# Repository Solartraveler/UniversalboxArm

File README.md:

# UniversalboxArm

## Idea

Have a box for experiments and easy testing with a CPU which is more powerful than an AVR (Arduino)
and uses less energy than a Raspberry Pi.
Then add some common peripherals and fit this into a case.

## Features

The following hardware has been added. Not everything is required to be populated on the PCB.

- Various 64Pin STM32 MCUs possible

    - STM32L452RET (80MHz, 160KiB RAM) tested

- Runs from USB power

- Can run from a LiFePO battery and charge it

- 2x red-green duo LEDs

- Four buttons

- LCD socket

    - 128x128 (ST7735, tested), 160x128 (ST7735, untested) or 320x240 (ILI9341, tested) RGB LCDs are possible

- Four Relays

- External flash with up to 8MiB

- RS232 level converter

- IR receiver

- WLAN with an ESP-01

- Two open collector outputs

- Several ESD protected in and outputs

- AVR coprocessor for resetting and charge control

## Status

### Software

#### DFU loader for the ARM

A loader for the STM32 MCU is feature complete.

- Can be used by the common dfu-util delivered by the usual Linux distributions (like Debian)

- Accepts applications within a common .tar file together with some metadata

    - With the STM32L452 having 160KiB RAM, the tar file may be up to 128KiB in size.
Needing 2.5KiB overhead for the .tar format and the metadata, the binary may be up to 125.5KiB in size and after starting can use the full 160KiB for code + data.
Executing from RAM results in about 80% of the speed compared with executing from flash with the same CPU frequency.

- The application can be run directly from the RAM or stored into the external flash

    - Transferring to RAM is much faster than writing to the flash. Also there is no worry about the internal flash lifetime.

- Formats the external flash as FAT filesystem

- Allows configuring one of the three LCD sizes

    - Configuration is stored on the external flash and can be read by other applications

- With the four keys and the LCD, applications can be selected from the external flash and run without an USB connection

    - Can set one application as autostarting on power-on

- Each application can have a short descriptive text and explanation image to be shown on the LCD

    - The text can be up to 1KiB long and is taken from the readme.md of each firmware

    - The image is 3 bit RGB and must have the size of the selected LCD or one of the possible smaller LCDs.
Moreover the compressed data needs to fit within 7000byte. Due to RAM constraints, each 4x4 pixel block can not display pixel with more than two different colors.

#### Firmware for the coprocessor

- A long press of the left key resets the ARM processor

- A long press of the right key toggles if a reset should start the DFU bootloader from ST or the application from the flash (most likely the DFU bootloader described above)

- Supports a SPI communication to the ARM processor

    - ARM processor can request a reset

    - ARM processor can enable a watchdog

- The battery can be charged

- A wakeup time for the ARM processor can be set

#### More software

Software testing all the hardware to be working as intended has been written for the ARM processor and the AVR coprocessor.

There is a implementation for using the 8MiB flash as USB pen drive.

One application implements an NTP client and uses the display as digital clock.

See [readme.md](src/apps/readme.md)

### Hardware

The PCB version 1 is working, but a lot of patching is required at several peripherals to use them.
With 380µA, the power down consumption is too high, as this would discharge a full battery within 65 days, and then the LiFePo must be considered defective.
The required changes are documented. Recreating a PCB version 1 is discouraged.
Instead the required changes need to be integrated into a version 2.

Milling the case is done.

See [readme.md](case/readme.md)

## Using a breadboard

Without soldering an own PCB, some of the apps can be used together with a Nucleo evaluation board from ST.
Then it is just a connection of some wires.
Instead of the onboard flash, the SD card can be used to store settings.
Many of the breakout boards for the LCDs already have a SD card slot on the backside.
The serial port is provided by the nucleo board over USB itself.
One LED and one button is provided by the nucleo board, thee additional buttons can be connected, everthing else is currently missing support.
Currently only the blinky-hal, test-everything and adc-scope apps have been tested on a nucleo with a STM32F411.
As the used board with a STM32F411 only has 128KiB of RAM, it will never be possible to load and execute all apps from RAM there.
However all could made working when running from flash.

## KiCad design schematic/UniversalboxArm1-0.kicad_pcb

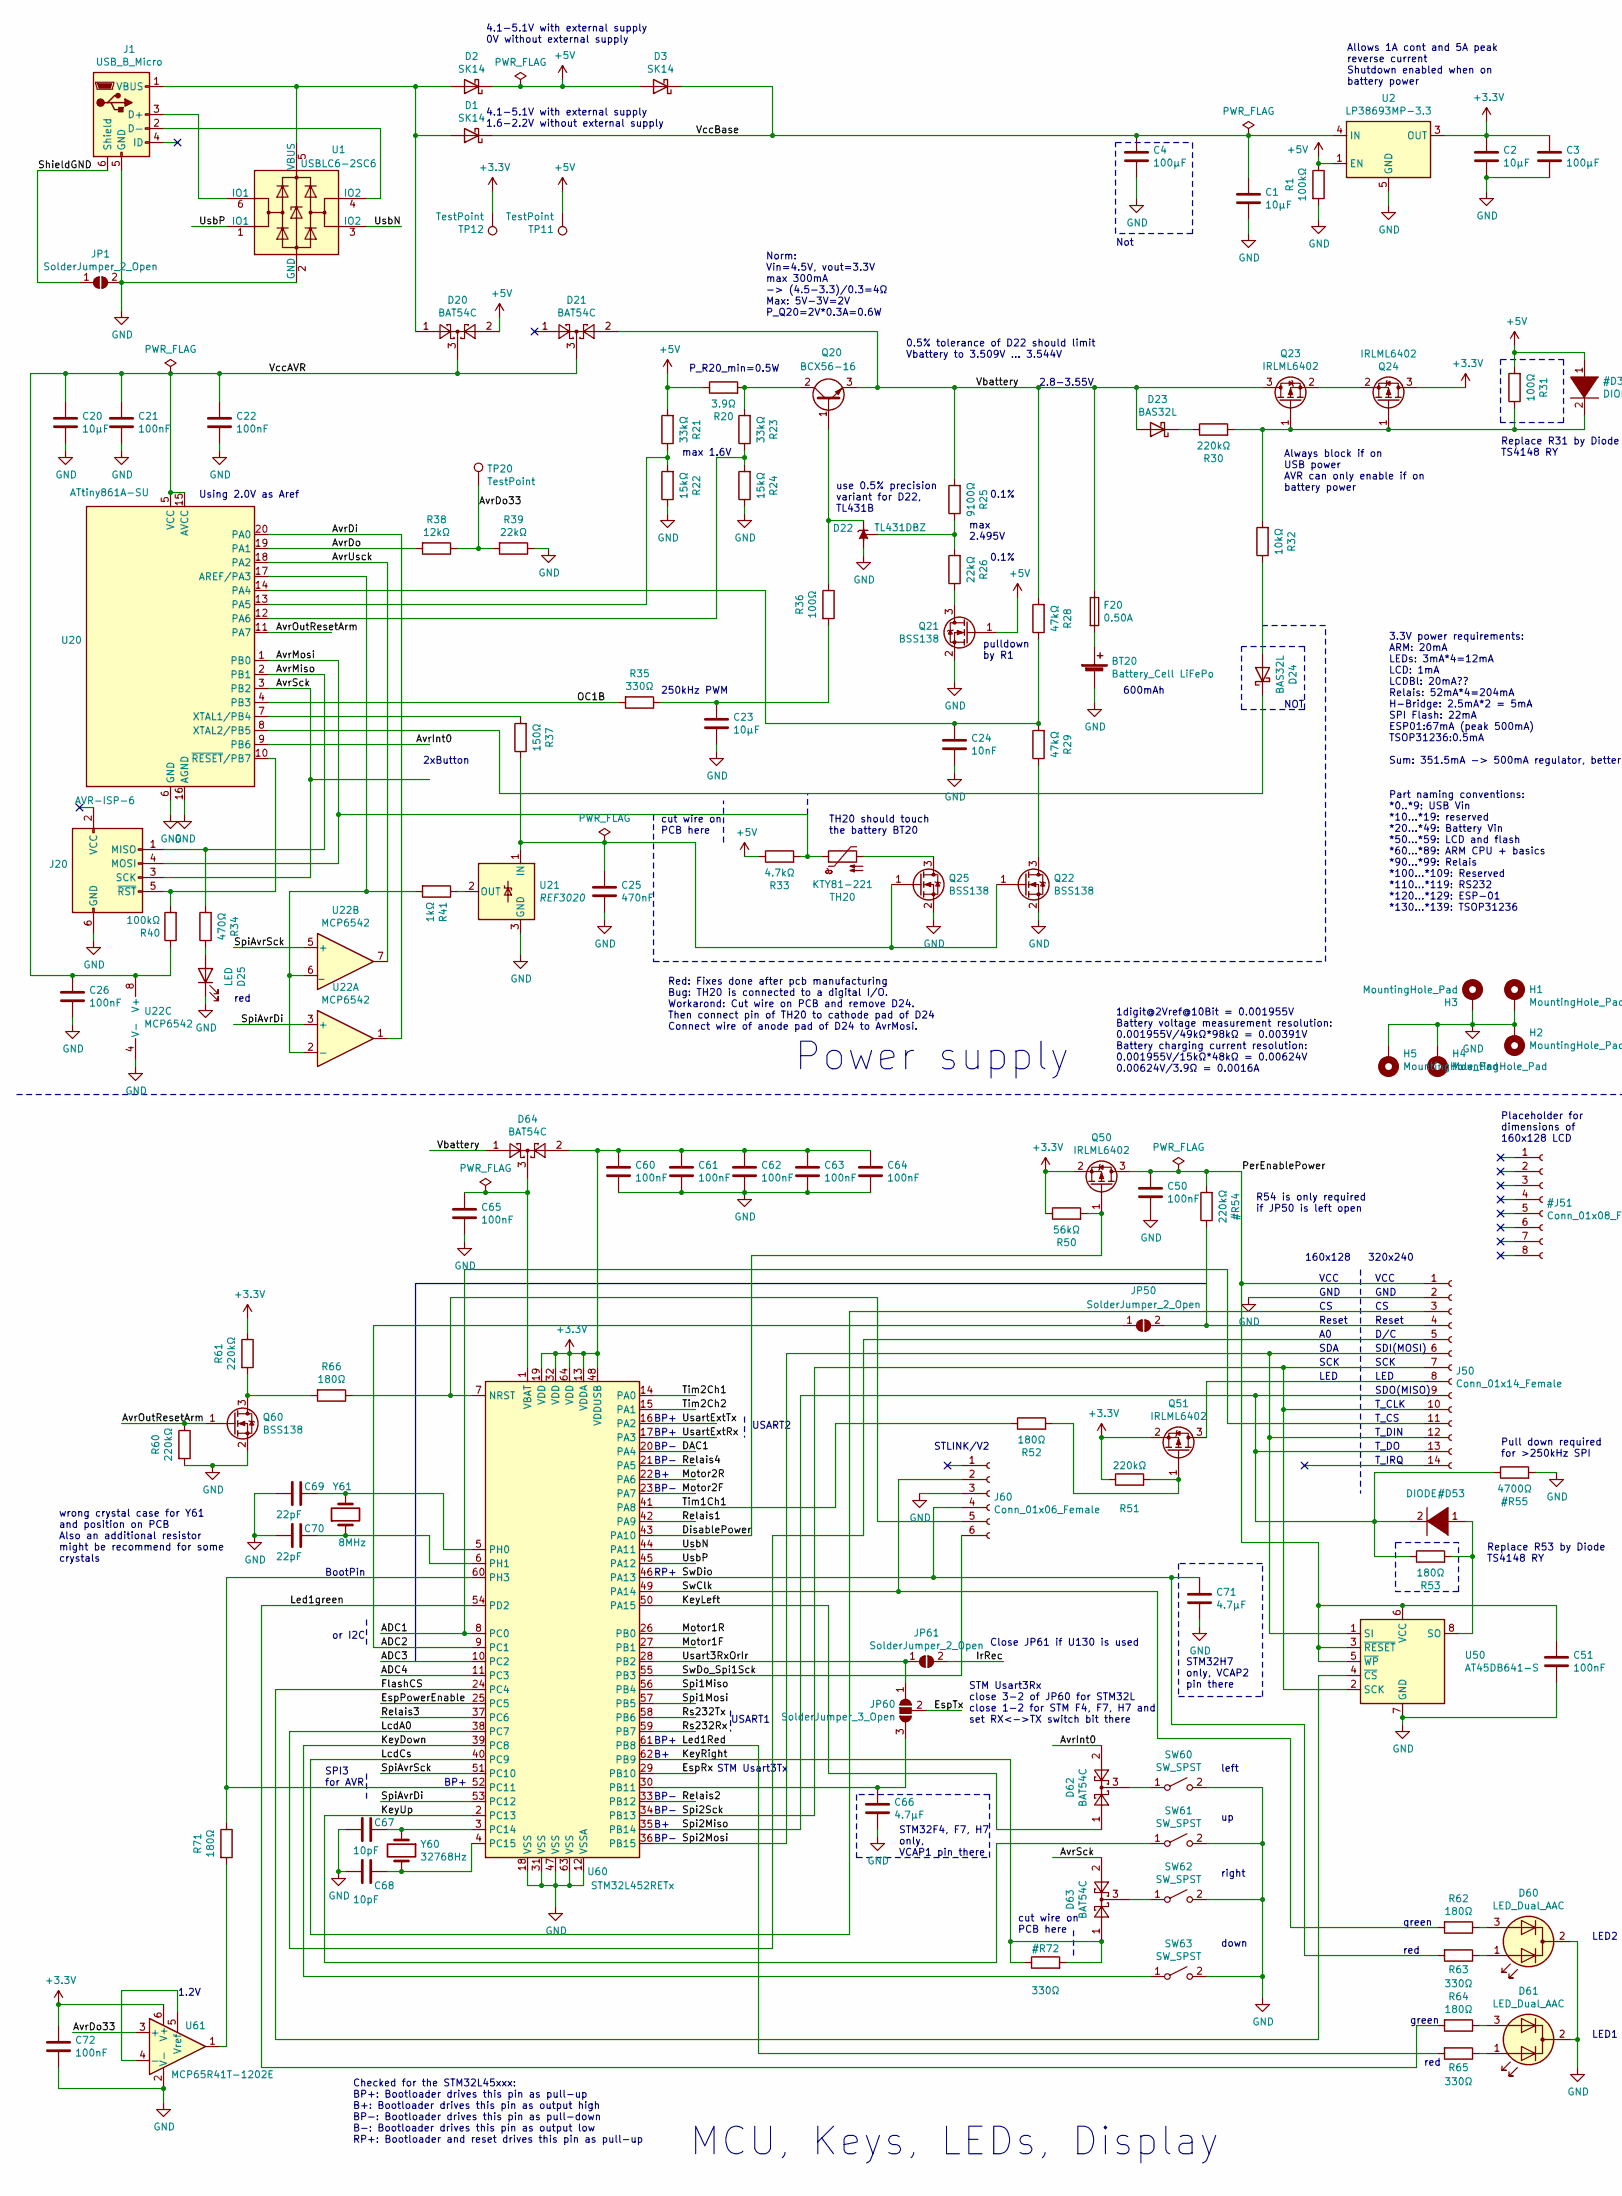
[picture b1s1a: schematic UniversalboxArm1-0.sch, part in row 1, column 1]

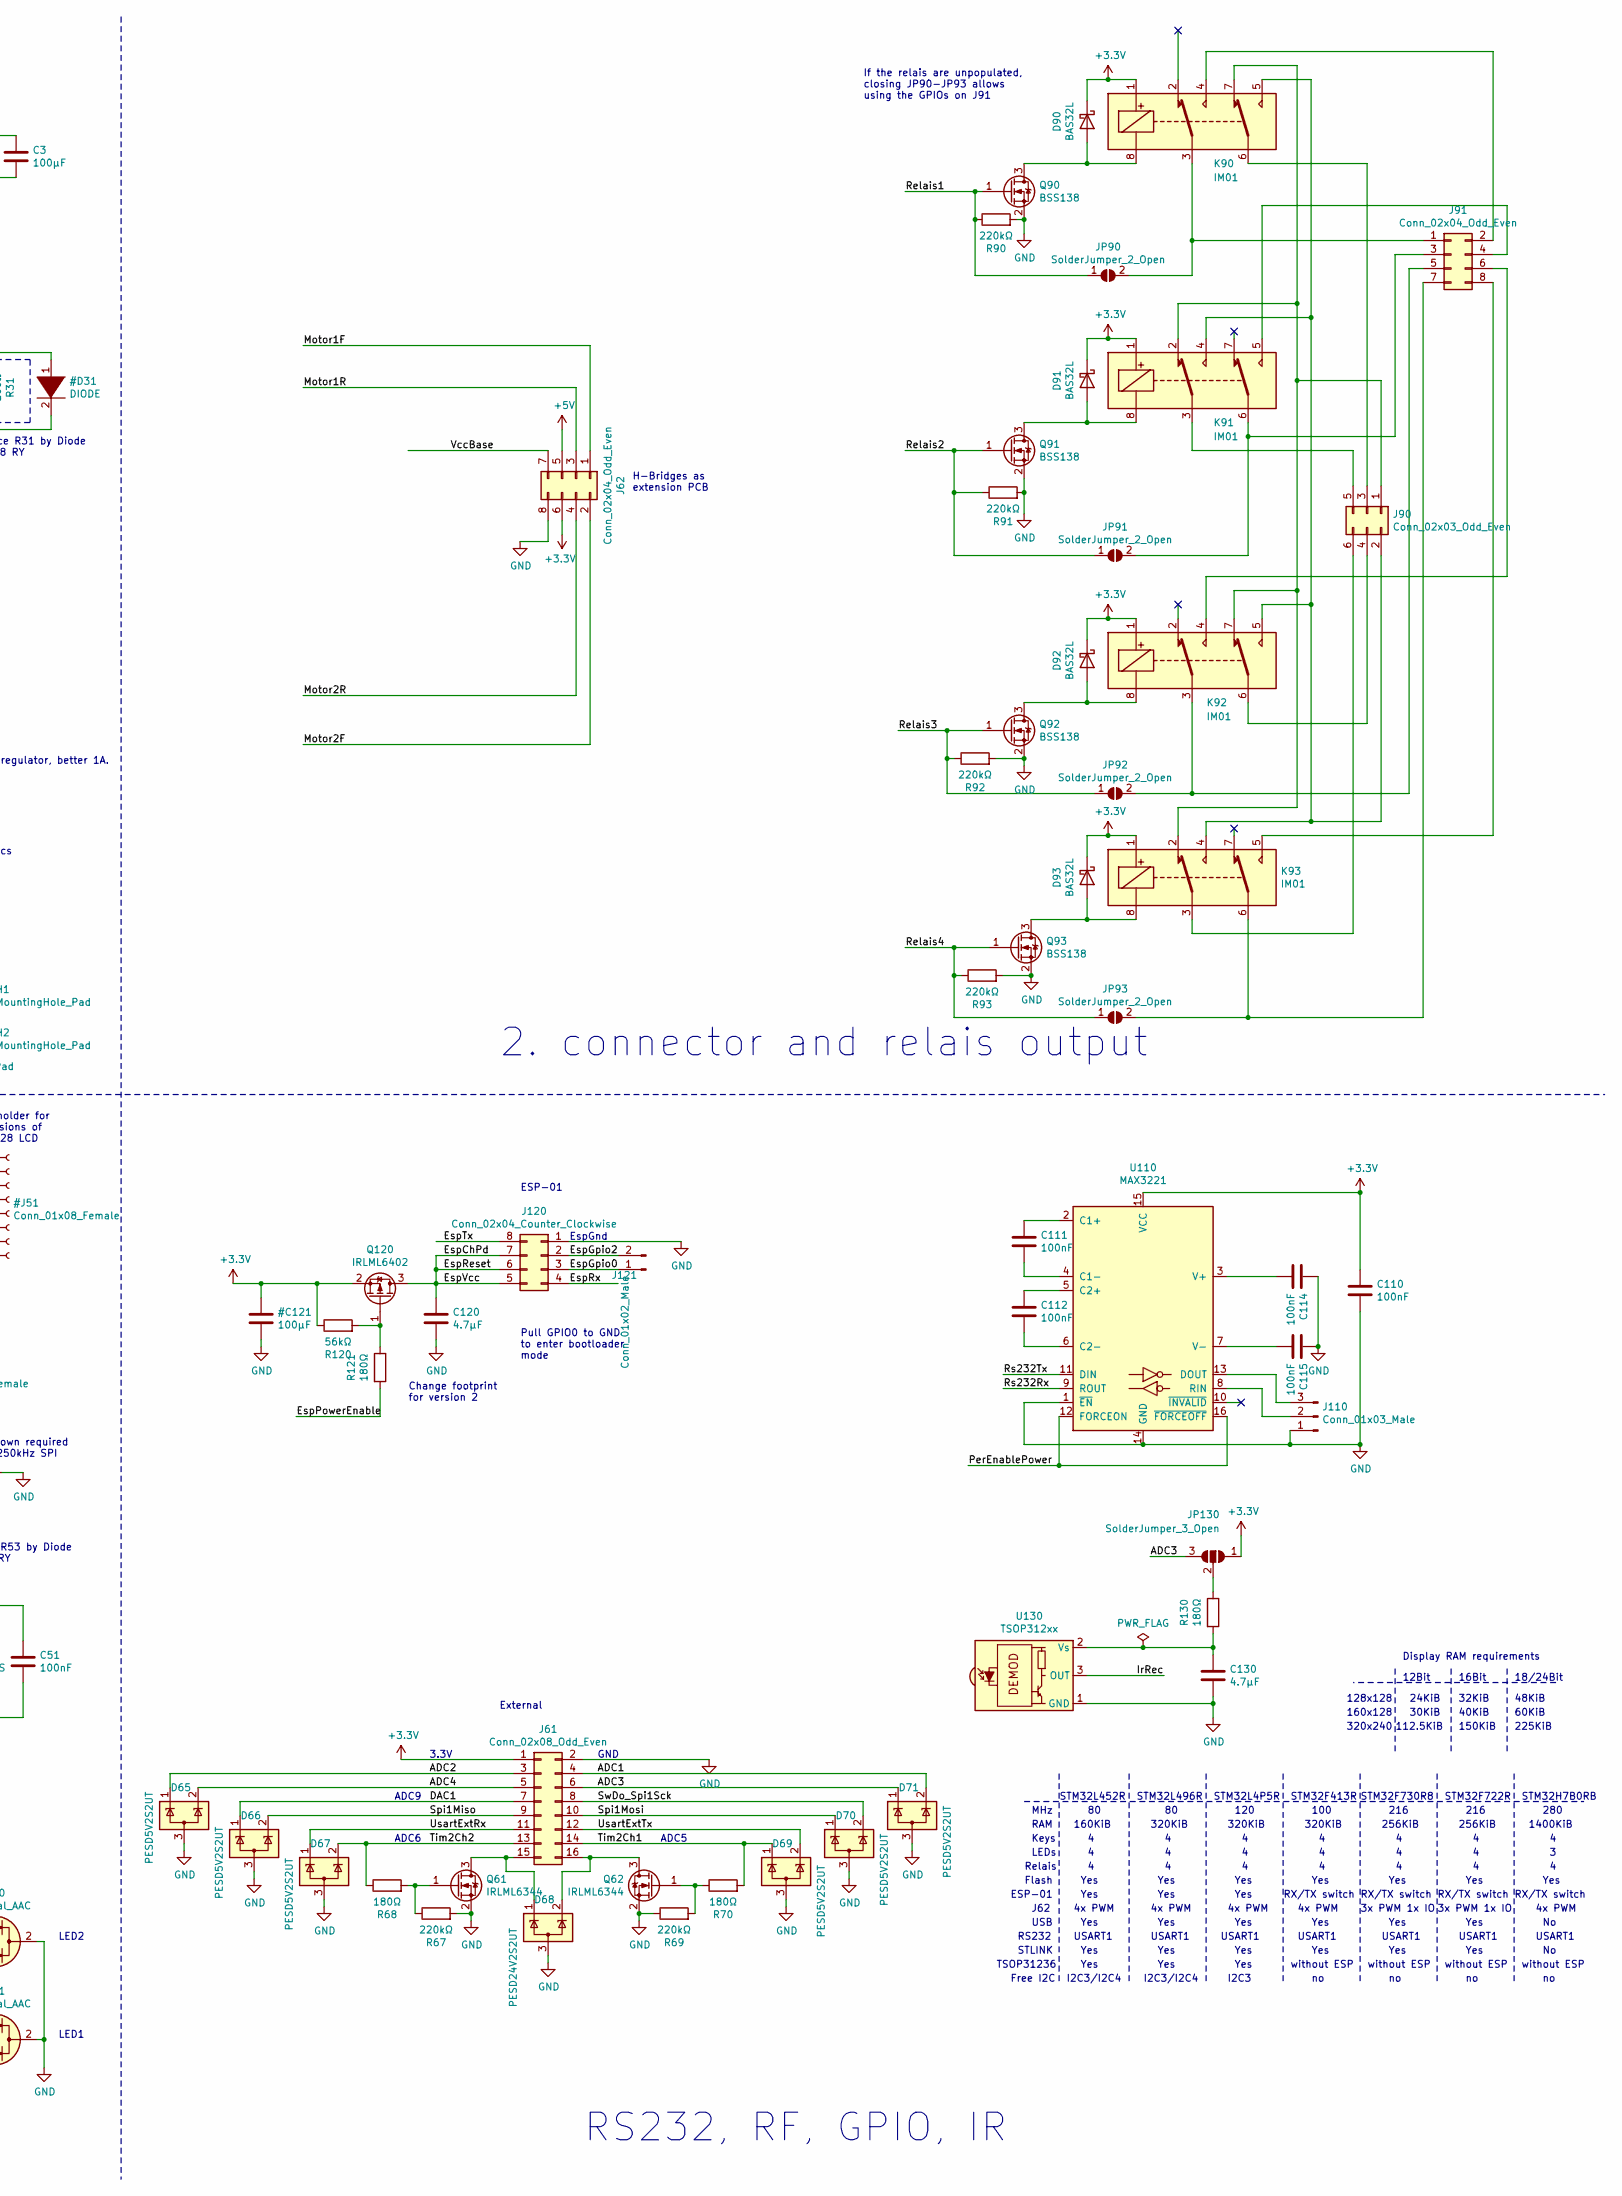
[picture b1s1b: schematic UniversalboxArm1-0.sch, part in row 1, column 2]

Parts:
BT20: Battery_Cell LiFePo; Keystone_Holder_1xAA_1015
C1, C2, C20, C23: 10µF; C_0805_2012Metric_Pad1.15x1.40mm_HandSolder
C3, C4: 100µF; C_1206_3216Metric_Pad1.33x1.80mm_HandSolder
C21, C22, C26, C50, C51, C60, C61, C62, C63, C64, C65, C72, C110, C111, C112, C114, C115: 100nF; C_0805_2012Metric_Pad1.15x1.40mm_HandSolder
C24: 10nF; C_0805_2012Metric_Pad1.15x1.40mm_HandSolder
C25: 470nF; C_0805_2012Metric_Pad1.15x1.40mm_HandSolder
C66, C71, C130: 4.7µF; C_0805_2012Metric_Pad1.15x1.40mm_HandSolder
C67, C68: 10pF; C_0805_2012Metric_Pad1.15x1.40mm_HandSolder
C69, C70: 22pF; C_0805_2012Metric_Pad1.15x1.40mm_HandSolder
C120: 4.7µF; C_1206_3216Metric_Pad1.33x1.80mm_HandSolder
D1, D2, D3: SK14; D_SMA
D20, D21, D62, D63, D64: BAT54C; SOT-23
D22: TL431DBZ; SOT-23
D23, D24, D90, D91, D92, D93: BAS32L; D_MiniMELF
D25: LED; LED_D3.0mm
D60, D61: LED_Dual_AAC; LED_D3.0mm-3
D65, D66, D67, D69, D70, D71: PESD5V2S2UT; SOT-23
D68: PESD24V2S2UT; SOT-23
F20: 0.50A; SFM_OMNI-BLOK_Handsolder
H1, H2, H3, H4, H5: MountingHole_Pad; MountingHole_3.2mm_M3_Pad
J1: USB_B_Micro; USB_Micro-B_Amtek-MIUSB-F5M-BBX-U_Handsolder
J20: AVR-ISP-6; PinHeader_2x03_P2.54mm_Vertical
J50: Conn_01x14_Female; LCD_320x240_2.4
J60: Conn_01x06_Female; PinHeader_1x06_P2.54mm_Vertical
J61: Conn_02x08_Odd_Even; PinHeader_2x08_P2.54mm_Vertical
J62, J91: Conn_02x04_Odd_Even; PinHeader_2x04_P2.54mm_Vertical
J90: Conn_02x03_Odd_Even; PinHeader_2x03_P2.54mm_Vertical
J110: Conn_01x03_Male; PinHeader_1x03_P2.54mm_Vertical
J120: Conn_02x04_Counter_Clockwise; PinSocket_ESP-01
J121: Conn_01x02_Male; PinHeader_1x02_P2.54mm_Vertical
JP1, JP50, JP61, JP90, JP91, JP92, JP93: SolderJumper_2_Open; SolderJumper-2_P1.3mm_Open_RoundedPad1.0x1.5mm
JP60, JP130: SolderJumper_3_Open; SolderJumper-3_P1.3mm_Open_RoundedPad1.0x1.5mm
K90, K91, K92, K93: IM01; Relay_DPDT_Omron_G6K-2F-Y
Q20: BCX56-16; SOT-89-3
Q21, Q22, Q25, Q60, Q90, Q91, Q92, Q93: BSS138; SOT-23
Q23, Q24, Q50, Q51, Q120: IRLML6402; SOT-23
Q61, Q62: IRLML6344; SOT-23
R1, R40: 100kΩ; R_0805_2012Metric_Pad1.15x1.40mm_HandSolder
R20: 3.9Ω; R_MELF_MMB-0207
R21, R23: 33kΩ; R_0805_2012Metric_Pad1.15x1.40mm_HandSolder
R22, R24: 15kΩ; R_0805_2012Metric_Pad1.15x1.40mm_HandSolder
R25: 9100Ω; R_0805_2012Metric_Pad1.15x1.40mm_HandSolder
R26, R39: 22kΩ; R_0805_2012Metric_Pad1.15x1.40mm_HandSolder
R28, R29: 47kΩ; R_0805_2012Metric_Pad1.15x1.40mm_HandSolder
R30, R51, R60, R61, R67, R69, R90, R91, R92, R93: 220kΩ; R_0805_2012Metric_Pad1.15x1.40mm_HandSolder
R31, R36: 100Ω; R_0805_2012Metric_Pad1.15x1.40mm_HandSolder
R32: 10kΩ; R_0805_2012Metric_Pad1.15x1.40mm_HandSolder
R33: 4.7kΩ; R_0805_2012Metric_Pad1.15x1.40mm_HandSolder
R34: 470Ω; R_0805_2012Metric_Pad1.15x1.40mm_HandSolder
R35, R63, R65: 330Ω; R_0805_2012Metric_Pad1.15x1.40mm_HandSolder
R37: 150Ω; R_0805_2012Metric_Pad1.15x1.40mm_HandSolder
R38: 12kΩ; R_0805_2012Metric_Pad1.15x1.40mm_HandSolder
R41: 1kΩ; R_0805_2012Metric_Pad1.15x1.40mm_HandSolder
R50, R120: 56kΩ; R_0805_2012Metric_Pad1.15x1.40mm_HandSolder
R52, R53, R62, R64, R66, R68, R70, R71, R121, R130: 180Ω; R_0805_2012Metric_Pad1.15x1.40mm_HandSolder
SW60, SW61, SW62, SW63: SW_SPST; SW_PUSH_6mm_H13mm
TH20: KTY81-221; TO-92-2
TP11, TP12, TP20: TestPoint; TestPoint_THTPad_D1.5mm_Drill0.7mm
U1: USBLC6-2SC6; SOT-23-6
U2: LP38693MP-3.3; SOT-223-5
U20: ATtiny861A-SU; SOIC-20W_7.5x12.8mm_P1.27mm
U21: REF3020; SOT-23
U22: MCP6542; SOIC-8_3.9x4.9mm_P1.27mm
U50: AT45DB641-S; SO-8_5.3x6.2mm_P1.27mm
U60: STM32L452RETx; LQFP-64_10x10mm_P0.5mm_Handsoldering
U61: MCP65R41T-1202E; SOT-23-6_Handsoldering
U110: MAX3221; SSOP-16_5.3x6.2mm_P0.65mm_Handsolder
U130: TSOP312xx; Vishay_CAST-3Pin
Y60: 32768Hz; Crystal_HC49-U_Vertical
Y61: 8MHz; Crystal_MP03

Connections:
/ADC1: D71.2 (K), J50.11, J61.4, U60.8 (PC0)
/ADC2: D65.1 (K), J61.3, JP50.1 (A), U60.9 (PC1)
/ADC3: D71.1 (K), J61.6, JP130.3 (B), U60.10 (PC2)
/ADC4: D65.2 (K), J61.5, U60.11 (PC3)
/AvrDi: U20.20 (PA0), U22.1
/AvrDo: R38.2, U20.19 (PA1)
/AvrDo33: R38.1, R39.2, TP20.1, U61.3 (+)
/AvrInt0: D62.2, U20.9 (PB6)
/AvrMiso: J20.1 (MISO), R34.2, U20.2 (PB1)
/AvrMosi: J20.4 (MOSI), R33.2, TH20.1, U20.1 (PB0)
/AvrOutResetArm: Q60.1 (G), R60.1, U20.11 (PA7)
/AvrSck: D63.2, J20.3 (SCK), U20.3 (PB2)
/AvrUsck: U20.18 (PA2), U22.7
/DAC1: D66.1 (K), J61.7, U60.20 (PA4)
/DisablePower: Q50.1 (G), R50.2, U60.43 (PA10)
/EspChPd: C120.1, J120.5, J120.6, J120.7, Q120.3 (D)
/EspGpio0: J120.3, J121.1
/EspGpio2: J120.2, J121.2
/EspPowerEnable: R121.2, U60.25 (PC5)
/EspRx: J120.4, U60.29 (PB10)
/EspTx: J120.8, JP60.2 (C)
/FlashCS: U50.4 (~CS), U60.24 (PC4)
/IrRec: JP61.2 (B), U130.3 (OUT)
/KeyDown: SW63.1 (A), U60.39 (PC8)
/KeyLeft: D62.1, U60.50 (PA15)
/KeyRight: D63.1, U60.62 (PB9)
/KeyUp: SW61.1 (A), U60.2 (PC13)
/LcdA0: J50.5, U60.38 (PC7)
/LcdCs: J50.3, U60.40 (PC9)
/Led1Red: R65.2, U60.61 (PB8)
/Led1green: R64.2, U60.54 (PD2)
/Motor1F: J62.1, U60.27 (PB1)
/Motor1R: J62.3, U60.26 (PB0)
/Motor2F: J62.2, U60.23 (PA7)
/Motor2R: J62.4, U60.22 (PA6)
/OC1B: R35.2, U20.4 (PB3)
/Relais1: JP90.1 (A), Q90.1 (G), R90.1, U60.42 (PA9)
/Relais2: JP91.1 (A), Q91.1 (G), R91.1, U60.33 (PB12)
/Relais3: JP92.1 (A), Q92.1 (G), R92.1, U60.37 (PC6)
/Relais4: JP93.1 (A), Q93.1 (G), R93.1, U60.21 (PA5)
/Rs232Rx: U60.59 (PB7), U110.9 (ROUT)
/Rs232Tx: U60.58 (PB6), U110.11 (DIN)
/ShieldGND: J1.6 (Shield), JP1.1 (A)
/Spi1Miso: D66.2 (K), J61.9, U60.56 (PB4)
/Spi1Mosi: D70.1 (K), J61.10, U60.57 (PB5)
/Spi2Mosi: J50.6, J50.12, U50.1 (SI), U60.36 (PB15)
/Spi2Sck: J50.7, J50.10, U50.2 (SCK), U60.34 (PB13)
/SpiAvrDi: U22.3 (+), U60.53 (PC12)
/SpiAvrSck: U22.5 (+), U60.51 (PC10)
/SwClk: J60.2, R62.2, U60.49 (PA14)
/SwDio: C71.1, J60.4, R63.2, U60.46 (PA13)
/SwDo_Spi1Sck: D70.2 (K), J60.6, J61.8, U60.55 (PB3)
/Tim1Ch1: R52.1, U60.41 (PA8)
/Tim2Ch1: D69.1 (K), J61.14, R70.2, U60.14 (PA0)
/Tim2Ch2: D67.2 (K), J61.13, R68.1, U60.15 (PA1)
/Usart3RxOrIr: JP60.1 (A), JP61.1 (A), U60.28 (PB2)
/UsartExtRx: D67.1 (K), J61.11, U60.17 (PA3)
/UsartExtTx: D69.2 (K), J61.12, U60.16 (PA2)
/UsbN: U1.3 (IO2), U60.44 (PA11)
/UsbP: U1.1 (IO1), U60.45 (PA12)
/Vbattery: D21.2, D23.2 (A), D64.1, F20.1, Q20.3 (E), Q23.3 (D), R25.2, R28.2
/VccAVR: C20.1, C21.1, C22.1, C26.1, D20.3, D21.3, R40.1, U20.5 (VCC), U20.15 (AVCC), U22.8 (V+)
/VccBase: C1.1, C4.1, D1.1 (K), D3.1 (K), J62.7, U2.4 (IN)
unnamed: BT20.1 (+), F20.2
unnamed: C23.1, R35.1, R36.2
unnamed: C24.1, R28.1, R29.2, U20.14 (PA4)
unnamed: C25.1, Q22.1 (G), Q25.1 (G), R37.1, U21.1 (IN)
unnamed: C65.1, D64.3, U60.1 (VBAT)
unnamed: C66.1, JP60.3 (B), U60.30 (PB11)
unnamed: C67.1, U60.3 (PC14), Y60.1
unnamed: C68.1, U60.4 (PC15), Y60.2
unnamed: C69.1, U60.5 (PH0), Y61.2
unnamed: C70.1, U60.6 (PH1), Y61.1
unnamed: C111.1, U110.2 (C1+)
unnamed: C111.2, U110.4 (C1-)
unnamed: C112.1, U110.5 (C2+)
unnamed: C112.2, U110.6 (C2-)
unnamed: C114.2, U110.3 (V+)
unnamed: C115.2, U110.7 (V-)
unnamed: C130.1, R130.2, U130.2 (Vs)
unnamed: D1.2 (A), D2.2 (A), D20.1, J1.1 (VBUS), U1.5 (VBUS)
unnamed: D22.1 (K), Q20.1 (B), R36.1
unnamed: D22.2 (REF), R25.1, R26.2
unnamed: D23.1 (K), R30.1
unnamed: D24.1 (K), U20.8 (XTAL2/PB5)
unnamed: D24.2 (A), R32.1
unnamed: D25.2 (A), R34.1
unnamed: D60.1 (A1), R63.1
unnamed: D60.3 (A2), R62.1
unnamed: D61.1 (A1), R65.1
unnamed: D61.3 (A2), R64.1
unnamed: D62.3, SW60.1 (A)
unnamed: D63.3, SW62.1 (A)
unnamed: D68.1 (K), J61.15, Q61.3 (D)
unnamed: D68.2 (K), J61.16, Q62.3 (D)
unnamed: D90.2 (A), K90.8, Q90.3 (D)
unnamed: D91.2 (A), K91.8, Q91.3 (D)
unnamed: D92.2 (A), K92.8, Q92.3 (D)
unnamed: D93.2 (A), K93.8, Q93.3 (D)
unnamed: J1.2 (D-), U1.4 (IO2)
unnamed: J1.3 (D+), U1.6 (IO1)
unnamed: J20.5 (~RST), R40.2, U20.10 (~RESET~/PB7)
unnamed: J50.8, Q51.3 (D)
unnamed: J60.5, R66.1, U60.7 (NRST)
unnamed: J90.1, K90.7, K91.2, K92.7, K93.2
unnamed: J90.2, K90.5, K91.4, K92.5, K93.4
unnamed: J90.3, K90.6
unnamed: J90.4, K92.6
unnamed: J90.5, K91.3
unnamed: J90.6, K93.3
unnamed: J91.1, JP90.2 (B), K90.3
unnamed: J91.2, K90.4
unnamed: J91.3, JP91.2 (B), K91.6
unnamed: J91.4, K91.5
unnamed: J91.5, JP92.2 (B), K92.3
unnamed: J91.6, K92.4
unnamed: J91.7, JP93.2 (B), K93.6
unnamed: J91.8, K93.5
unnamed: J110.2, U110.8 (RIN)
unnamed: J110.3, U110.13 (DOUT)
unnamed: JP130.2 (C), R130.1
unnamed: Q20.2 (C), R20.2, R23.2
unnamed: Q21.3 (D), R26.1
unnamed: Q22.3 (D), R29.1
unnamed: Q23.2 (S), Q24.2 (S)
unnamed: Q25.3 (D), TH20.2
unnamed: Q51.1 (G), R51.2, R52.2
unnamed: Q60.3 (D), R61.2, R66.2
unnamed: Q61.1 (G), R67.1, R68.2
unnamed: Q62.1 (G), R69.2, R70.1
unnamed: Q120.1 (G), R120.2, R121.1
unnamed: R21.1, R22.2, U20.13 (PA5)
unnamed: R23.1, R24.2, U20.12 (PA6)
unnamed: R37.2, U20.7 (XTAL1/PB4)
unnamed: R41.1, U21.2 (OUT)
unnamed: R41.2, U20.17 (AREF/PA3), U22.2 (-), U22.6 (_)
unnamed: R71.1, U60.52 (PC11), U60.60 (PH3)
unnamed: R71.2, U61.1
unnamed: U61.4 (-), U61.5 (Vref)

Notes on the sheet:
600mAh
3.3V power requirements: ARM: 20mA LEDs: 3mA*4=12mA LCD: 1mA LCDBl: 20mA?? Relais: 52mA*4=204mA H-Bridge: 2.5mA*2 = 5mA SPI Flash: 22mA ESP01:67mA (peak 500mA) TSOP31236:0.5mA Sum: 351.5mA -> 500mA regulator, better 1A.
250kHz PWM
4.1-5.1V with external supply 0V without external supply
2.8-3.55V
Norm: Vin=4.5V, vout=3.3V max 300mA -> (4.5-3.3)/0.3=4Ω Max: 5V-3V=2V P_Q20=2V*0.3A=0.6W
Always block if on USB power AVR can only enable if on battery power
use 0.5% precision variant for D22, TL431B
max 2.495V
Allows 1A cont and 5A peak reverse current Shutdown enabled when on battery power
4.1-5.1V with external supply 1.6-2.2V without external supply
Using 2.0V as Aref
TH20 should touch the battery BT20
red
P_R20_min=0.5W
2xButton
max 1.6V
1digit@2Vref@10Bit = 0.001955V Battery voltage measurement resolution: 0.001955V/49kΩ*98kΩ = 0.00391V Battery charging current resolution: 0.001955V/15kΩ*48kΩ = 0.00624V 0.00624V/3.9Ω = 0.0016A
Power supply
2. connector and relais output
left
right
down
pulldown by R1
STM32F4, F7, H7 only, VCAP1 pin there
Placeholder for dimensions of 160x128 LCD
SPI3 for AVR
320x240
160x128
VCC
GND
Reset
SDA
SCK
LED
D/C
SDI(MOSI)
SDO(MISO)
T_CLK
T_CS

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
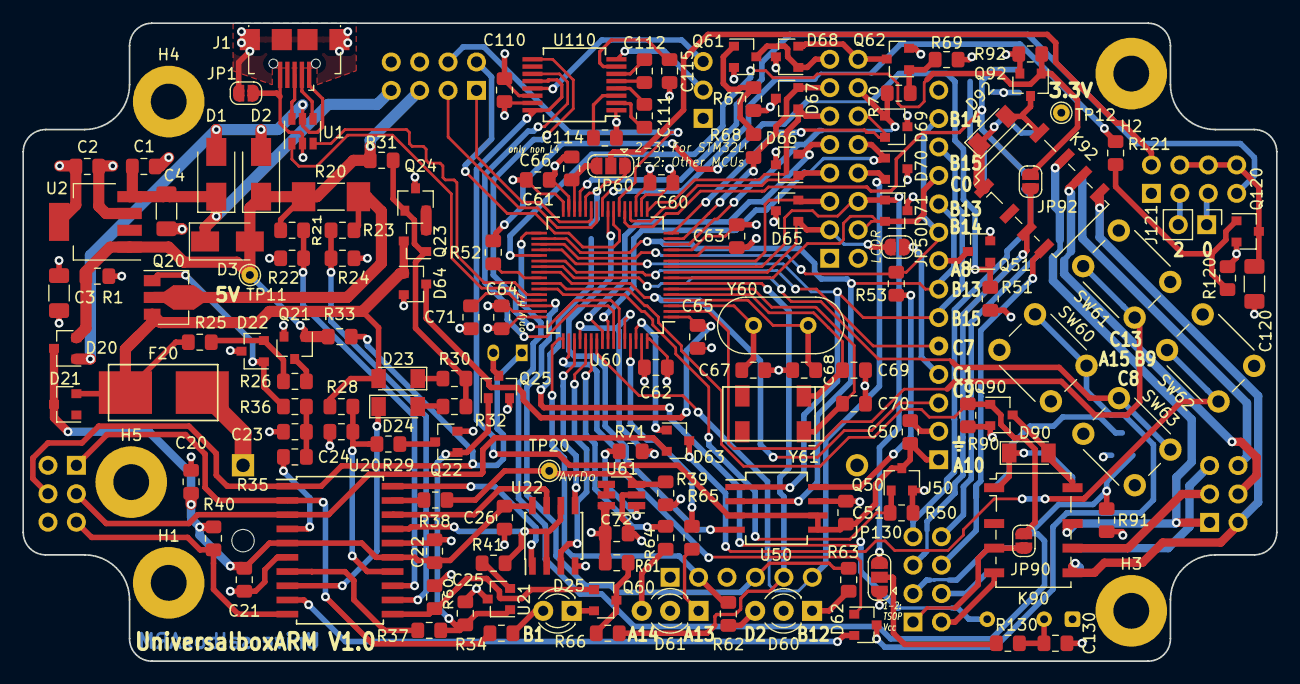
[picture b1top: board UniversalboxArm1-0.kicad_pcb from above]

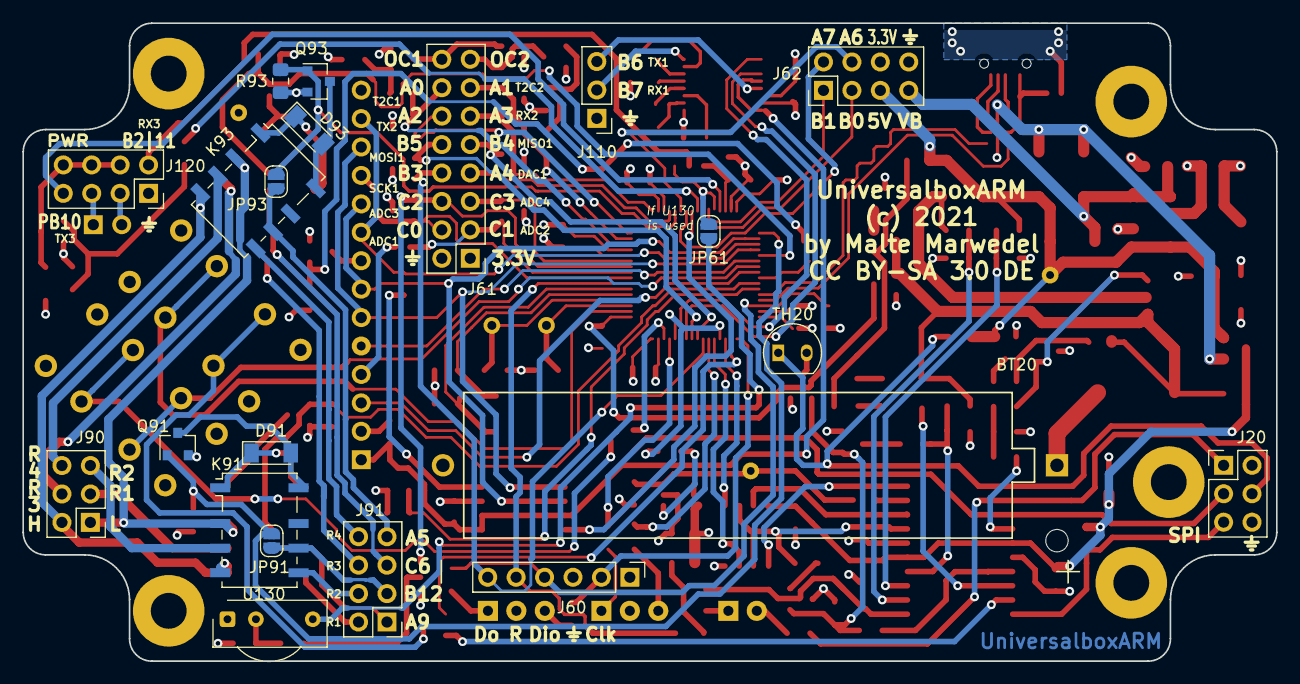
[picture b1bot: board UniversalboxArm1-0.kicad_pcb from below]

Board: 4 copper layers, 112.0 x 57.0 mm, 170 parts (21 on the bottom side), 147 nets.

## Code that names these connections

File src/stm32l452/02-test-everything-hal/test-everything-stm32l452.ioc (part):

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PB13.GPIOParameters=GPIO_Label
PC7.GPIOParameters=GPIO_Label
PA15\ (JTDI).GPIOParameters=GPIO_PuPd,GPIO_Label
PA14\ (JTCK/SWCLK).GPIOParameters=GPIO_Label
Mcu.UserName=STM32L452RETx
PB10.Mode=Asynchronous
PH0-OSC_IN\ (PH0).Signal=RCC_OSC_IN
PC10.Signal=GPIO_Output
PC12.Signal=GPIO_Output
PB14.GPIO_Label=PerSpiMiso
PA0.GPIO_Label=Extern14
PC0.GPIOParameters=GPIO_Label
PA9.GPIOParameters=GPIO_Label
PC0.GPIO_Label=Extern4
PC6.GPIO_Label=Relay3
PA3.GPIOParameters=GPIO_Label
PA6.GPIO_Label=Intern4
PB0.GPIO_Label=Intern3
PB6.GPIO_Label=Rs232Tx
PA15\ (JTDI).Signal=GPIO_Input
PD2.GPIOParameters=GPIO_Label
PC15-OSC32_OUT\ (PC15).Mode=LSE-External-Oscillator
PC13.GPIO_Label=KeyUp
PB13.GPIO_Label=PerSpiSck
PB11.Signal=USART3_RX
PB3\ (JTDO/TRACESWO).GPIOParameters=GPIO_Label
PB13.Signal=SPI2_SCK
PB15.Signal=SPI2_MOSI
PA2.GPIOParameters=GPIO_Label
PB5.GPIOParameters=GPIO_Label
PC14-OSC32_IN\ (PC14).Mode=LSE-External-Oscillator
PA14\ (JTCK/SWCLK).Signal=GPIO_Output
PC1.GPIOParameters=GPIO_Label
PB6.Signal=USART1_TX
PC7.Signal=GPIO_Output
PB6.Mode=Asynchronous
PC3.Signal=ADCx_IN4
PA8.GPIOParameters=PinState,GPIO_Label
PH1-OSC_OUT\ (PH1).Mode=HSE-External-Oscillator
RCC.HSE_VALUE=16000000
PB2.Signal=GPIO_Input
PB12.GPIO_Label=Relay2
PB0.GPIOParameters=GPIO_Label
PA13\ (JTMS/SWDIO).GPIO_Label=Led2Red
PA1.GPIOParameters=GPIO_Label
PC4.GPIO_Label=FlashCs
PB14.Mode=Full_Duplex_Master
PB1.GPIO_Label=Intern1
PC11.GPIO_Label=AvrSpiMiso
PA10.GPIO_Label=PeripheralNPower
PC13.GPIO_PuPd=GPIO_PULLUP
PB7.Signal=USART1_RX
PA8.Signal=GPIO_Output
PB6.GPIOParameters=GPIO_Label
PA0.Signal=ADCx_IN5
PB7.GPIO_Label=Rs232Rx
PC8.GPIOParameters=GPIO_PuPd,GPIO_Label
Mcu.Package=LQFP64
PB9.Signal=GPIO_Input
PB1.Signal=GPIO_Input
PA6.Signal=GPIO_Input
PA2.GPIO_Label=Extern12
PA10.Signal=GPIO_Input
PB9.GPIO_PuPd=GPIO_PULLUP
PA5.GPIOParameters=GPIO_Label
PB14.GPIOParameters=GPIO_Label
PA14\ (JTCK/SWCLK).GPIO_Label=Led2Green
PB5.GPIO_Label=Extern10
PC5.Signal=GPIO_Output
PB13.Mode=Full_Duplex_Master
PB10.GPIOParameters=GPIO_Label
PH0-OSC_IN\ (PH0).Mode=HSE-External-Oscillator
PA4.GPIO_Label=Extern7
PC2.GPIO_Label=IrPower
PC4.GPIOParameters=GPIO_Label
PA8.PinState=GPIO_PIN_SET
PA3.Signal=ADCx_IN8
PA6.GPIOParameters=GPIO_Label
PB3\ (JTDO/TRACESWO).GPIO_Label=Extern8
PB8.GPIOParameters=GPIO_Label
PB9.GPIO_Label=KeyRight
PC10.GPIO_Label=AvrSpiSck
PC9.GPIO_Label=LcdCs
PC13.Signal=GPIO_Input
PA9.GPIO_Label=Relay1
PC11.Signal=GPIO_Input
PC8.Signal=GPIO_Input
PC2.Signal=GPIO_Output
PC4.Signal=GPIO_Output
PC6.Signal=GPIO_Output
PB11.GPIO_Label=EspTxArmRx
PC15-OSC32_OUT\ (PC15).Signal=RCC_OSC32_OUT
PC0.Signal=ADCx_IN1
PC11.GPIOParameters=GPIO_Label
PA13\ (JTMS/SWDIO).GPIOParameters=GPIO_Label
PH1-OSC_OUT\ (PH1).Signal=RCC_OSC_OUT
PB9.GPIOParameters=GPIO_PuPd,GPIO_Label
PC3.GPIOParameters=GPIO_Label
PC8.GPIO_Label=KeyDown
PC12.GPIOParameters=GPIO_Label
PB8.GPIO_Label=Led1Red
PB4\ (NJTRST).GPIOParameters=GPIO_Label
PA8.GPIO_Label=LcdBacklight
PB11.Mode=Asynchronous
PB3\ (JTDO/TRACESWO).Signal=GPIO_Input
PB10.GPIO_Label=EspRxArmTx
PB7.GPIOParameters=GPIO_Label
PC5.GPIOParameters=GPIO_Label
PB2.GPIOParameters=GPIO_Label
PA9.Signal=GPIO_Output
PB11.GPIOParameters=GPIO_Label
PA1.Signal=ADCx_IN6
PB10.Signal=USART3_TX
PB14.Signal=SPI2_MISO
PA5.Signal=GPIO_Output
board=custom
PB15.Mode=Full_Duplex_Master
PB15.GPIO_Label=PerSpiMosi
PC13.GPIOParameters=GPIO_PuPd,GPIO_Label
PC2.GPIOParameters=GPIO_Label
PC1.GPIO_Label=Extern3
PA1.GPIO_Label=Extern13
PA10.GPIOParameters=GPIO_Label
PA15\ (JTDI).GPIO_PuPd=GPIO_PULLUP
PA4.GPIOParameters=GPIO_Label
PC10.GPIOParameters=GPIO_Label
PB15.GPIOParameters=GPIO_Label
PA15\ (JTDI).GPIO_Label=KeyLeft
PC9.GPIOParameters=GPIO_Label
Mcu.Name=STM32L452R(C-E)Tx
PA2.Signal=ADCx_IN7
PC7.GPIO_Label=LcdA0
PC8.GPIO_PuPd=GPIO_PULLUP
PA4.Signal=ADCx_IN9
PB5.Signal=GPIO_Input
PA7.GPIO_Label=Intern2
PA5.GPIO_Label=Relay4
PC5.GPIO_Label=EspPower
PC14-OSC32_IN\ (PC14).Signal=RCC_OSC32_IN
PC12.GPIO_Label=AvrSpiMosi
PB7.Mode=Asynchronous
PB2.GPIO_Label=IrIn
PA0.GPIOParameters=GPIO_Label
PC6.GPIOParameters=GPIO_Label
PB8.Signal=GPIO_Output
PC3.GPIO_Label=Extern6
PC9.Signal=GPIO_Output
PB4\ (NJTRST).GPIO_Label=Extern9
PD2.Signal=GPIO_Output
PB0.Signal=GPIO_Input
PA7.GPIOParameters=GPIO_Label
PC1.Signal=ADCx_IN2
PB12.GPIOParameters=GPIO_Label
PB12.Signal=GPIO_Output
PD2.GPIO_Label=Led1Green
PA13\ (JTMS/SWDIO).Signal=GPIO_Output
PA3.GPIO_Label=Extern11
PB1.GPIOParameters=GPIO_Label
PA7.Signal=GPIO_Input
PB4\ (NJTRST).Signal=GPIO_Input

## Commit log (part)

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2022-02-17 STM32: Use FIFO for debug prints. Allows using debug prints within interrupt handlers
2022-02-27 STM32: Add workig code for ILI9341 LCD. The code from ST was able to show a grey image and data could be read back from the status registers. But no correct image was visible on the LCD. The other in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
2022-03-07 STM32: Improve function to call another program. Allow to configure USB buffer size. The function for calling the DFU bootloader was moved to the common folder. Also interrupts are enabled when calli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
2022-03-14 Add JSMN json parser Version 1.1.0 without any modifications.
2022-03-17 STM32: Add early version of loader project. Implements DFU. GUI still missing.
2022-03-28 Common: Improve deinit of pc-simulation
    Disable LCD
    Disable Flash
    Call simulation deinit before program termination, if an other binary should be loaded.
2022-04-25 STM32: Add descriptive image to the 01-blinky-hal project
    The image can be shown by the Loader project with a checkin to follow.
2022-04-25 STM32: Implement GUI for the 03-loader project
    Also implement autostart option.
    The GUI is more or less complete - only the 128x128 LCD has been tested.
    Known Bugs:
    1. Saving transferred programs does not work if saving was not already
    requested during transfer.
    2. The 320x240 LCD likely does not work - because it has not been tested with
2022-05-08 STM32: Loader clean up code and reduce codesize
    Reduces codesize by about 4.5KiB.
    Removes unused RTC source files.
    Do not enable clock for unused UART.
    Add make target for whole binary disassembly.
2022-05-08 STM32: Loader: Shorten startup reset to 500ms
    Improves startup time
2022-05-15 Common: Prepare LCD functions to be used with DMA
    When using to buffers to be processed in the background, a waiting
    until the buffer can be used again is required. Normal LCD functions
    without DMA should provide the same interface.
    Clean up dead code too.
2022-05-23 Algorithm: Move json file from project to common folder
    Nothing CPU specific in it and useful for multiple projects.
2022-06-06 AVR: Fix timer frequency setup
    Was not working with F_CPU values above 1MHz
2022-06-29 AVR: Add request full charge. Add statistics to charger logic
2022-08-18 Common:Algorithm: Unify code for mounting flash disk and reading display config
    Allows reusing code across firmwares.
2022-08-21 AVR: 05-spi-with-charger: Improve power consumption, fix wakeup from deep power down
    Disabling the AVR hardware as far as possible reduces the power consumption of the
    AVR from ~200µA to ~90µA. Giving a total consumption of ~380µA when in ARM power off
    mode. Additional 285µA could be saved with a hardware fix.
    Bugfix: Wakeup from deep discharge prevention by keypress did not work.
2022-08-29 STM32: Unify PrintHex function
    Is useful even on a PC for unittests
2022-09-25 Common: Boxlib: Add µs delay and timestamp functions, add function to use PLL for CPU clock
    02-test-everythin: Now uses function from boxlib, instead of providing an own function
    for using the PLL as CPU clock
2022-09-28 STM32: Unify and extend DFU upload script
    Script now supports more options, one script is shared across all firmwares.
2022-10-02 AVR: Common: Make sure the timing control counts interrupts
    This allows catching up the time if not every interrupt was polled
    before the next interrupt arrived.
2022-10-03 Common: Algorithm: Fix typo in debug message
2022-10-22 STM32: 03-loader: Remove obsolete script file
2022-10-25 STM32: 06-usb-mass-storage: Fix linker scripts
    Should not use linker script for the loader.
    Only when loading to an address not used when the loader runs from RAM,
    the loader from RAM can load and run this project.
2022-10-31 Boxlib: Allow McuTimestampUs to be called from ISR or with locked interrupts
2022-11-05 Boxlib: Support more frequencies for the CPU and peripherals
2022-11-13 Common: Algorithm: Add time conversion functions
    Also enable tests for time conversion and femtoVsnprintf
2022-11-15 STM32: 07-ntp-clock: Write time from server to internal RTC, allow manual input
    Also add more error checking of returned timestamps.
    Wifi config now uses key "ap1" and "password1", to allow multiple access points.
    Debug information of the RTC can be printed.
    GUI, timezone support and setting the NTP server is missing.
2022-11-19 Common: Algorithm: Fix testcase for time function, run tests with CI
    Should have been run by the CI already.
2022-11-23 Common: Algorithm: Do not use double precision in imageDrawer
    This saves about 2K of code space later.
    Found with the -Wdouble-promotion compiler switch.
2022-11-26 Common: Algorithm: Add simple function for reading a file
2022-11-28 Common: Boxlib: Use systick with FreeRTOS and ST HAL
2022-12-04 Common: Pc-Simulator: Simulate FreeRTOS binary mutex on a PC
2022-12-20 Common: Algorithm: Implement strlcpy
    Like strncpy, but gurantees a \0 termination of the output.
2023-07-04 Common: Implement backlight control
2023-07-09 Common: Boxlib: Report more details in the case of an exception
2023-07-27 STM32: 09-gamebox: Convert all files to utf-8 encoding
    The original encoding was iso 8859-15.
2023-07-29 Boxlib: Fix thread safeness of flash and LCD access
    The flash access missed using the lock when writing.
    The LCD already released the lock after the first command was send
    and before the pixel data were sent.
2023-09-16 STM32: Add 10-infrared-decoder project
    The project uses the IRMP library and is feature complete.
2023-12-29 Utilities: Add documentation for udev rule
2024-01-31 Boxlib: Add fast ADC conversion with DMA transfer
2024-02-02 Algorithm: Fix compiler warning in utility.c
    "array subscript has type 'char'" was a legitimate warning, which could
    have resulted in an index out of bounds access in AsciiScanDec.
    The fixed implementation also saves some bytes of program memory.
2024-02-17 Apps: Unify stm32l4xx_hal_msp.c and system_stm32l4xx.c of several projects
    The current folder and build architecture does not allow to have
    .c or .h files in different folders with the same name. So the remaining
    apps 01..4 can not share the unified stm32l4xx_hal_msp.c and system_stm32l4xx.c
    because a different main.c (of which there is a unified version in the same
    folder) is needed.
    Larger architecture changes where which shared files is found might
2024-02-23 AVR: 05-spi-with-charger: Add coprocessor command to read out minimal battery voltage
    Reads out the minimal battery voltage since the last coprocessor start
2024-03-06 Apps: 01-blinky-hal: Unify linker scripts and headers. Support compiling for other CPU+board targets
    Providing the right external libraries, the sample now works on a STM32 Nucleo-64 board too.
2024-03-22 WIP: Working ADC with DMA on STM32F411
2024-04-04 Common: Boxlib: Add code for 16bit timer of STM32F411
    This needes changes to the existing STM32L4 code, as the inline functions
    do not work when headers are shared between different chip implentations.
    Also the include path for the 11-adc-scope app needs to be adjusted.
2024-04-08 Common: Boxlib: Fix getting Avref value for STM32L452
    This bug was introduced with commit #d38a9c1079, which only
    moved code around...
2024-05-09 Common: Boxlib: Fix AdcInputsSet, fix AdcSampleTimeSet, add print ADC registers, make AVRef input pin a constant, add pc-simulation of adcDma.c
    AdcInputsSet did not properly cleared registers SQR2, SQR3, SQR4, as result changing the selected inputs
    failed for the STM32F411 (for any number of inputs) and for the STM32L452 if more than 4 inputs were selected.
    AdcSampleTimeSet failed for the STM32F411 if more than 6 inputs were selected.
    The AVREF pin is now available as define.
    The ADC and corresponding DMA registers can be printed for debug purpose.
    Dummy functions for the pc-simulation are now available.
2024-05-09 Common: Boxlib: Fix compiler errors for STM32F411 and a warning for STM32L452
    Looks like some compiler versions allow the C++ style to ignore an unused parameter
    and some other report an error...
2024-06-15 Apps: 02-test-everything: Fix compiler warning
2024-07-13 Schematic: Add wiring of a Nucleo-64 board to the LCD and SD card
2025-03-10 ci: Fix runner failing - add imagemagick to installation
    Must have been in the runners by default before, now somehow not anylonger.
    From imagemagick, the 'identify' binary is used in some algorithm tests.
2025-03-18 AVR: some work in progress voltage changes
    Increase minimum voltage to start charger and keep charger on.
2025-03-29 Algorithm: Add a black-white framebuffer with scaling
    Scaling allows saving memory. This is not the fastest, but the most
    memory saving framebuffer of all. More memory could be saved by
    writing to the LCD directly, but this would be really slow.
2025-04-07 Apps: 06-usb-mass-storage: Use shared code
    Remove (nearly) duplicated files and use common headers instead.
    The version stays the same, as the output files are the same as before (binay identical).
2025-04-13 libmad: Replace version from SourceForge by version from codeberg
    While the version 0.15.1b from SourceForge produced proper results when running as
    32-bit application (testes on ARM and with -m32 gcc compiler switch on x64),
    the sound were choppy and at lower frequencies (slow down) when compiling as 64-bit.
    Tracking this down, this issue was solved by commit
    https://codeberg.org/tenacityteam/libmad/commit/a341af817d03c8e2b2ccb32c02edc03e3c8639a7
    The fork also includes several security fixes made by Debian. So it is generally
2025-04-18 WIP: 15-mp3-player: Play a mp3 file over 8 bit PWM output
    State:
    Playback on the PC works
    Playback on the ARM works but sometimes needs more output buffer
    to not have a break during browsing through the files at the same time.
2025-05-09 Apps: 02-test-everything-hal: Add more precise timing measurements to flash test
    Can be used to compare improvements of the SPI functions.
2025-05-15 Apps: Remove compilation of HAL code for SPI and DMA
    As this is not included by the linker, the output stays the same and therefore
    the version does not need to be incremented.
    02-test-everything is excluded because there might be tests added for comparing
    the own and the HAL implementation.
2025-07-21 Algorithm: Make internal functions of SD card driver accessible
    Making the functions non static allows the usage from other source files.
2025-08-05 WIP: Sdcard playground

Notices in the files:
schematic/UniversalboxArm1-0.kicad_pcb:
(c) 2021
CC BY-SA 3.0 DE
